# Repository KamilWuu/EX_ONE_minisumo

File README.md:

# EX_ONE_minisumo
# New dimension of minisumo robots.

faulhaber motors

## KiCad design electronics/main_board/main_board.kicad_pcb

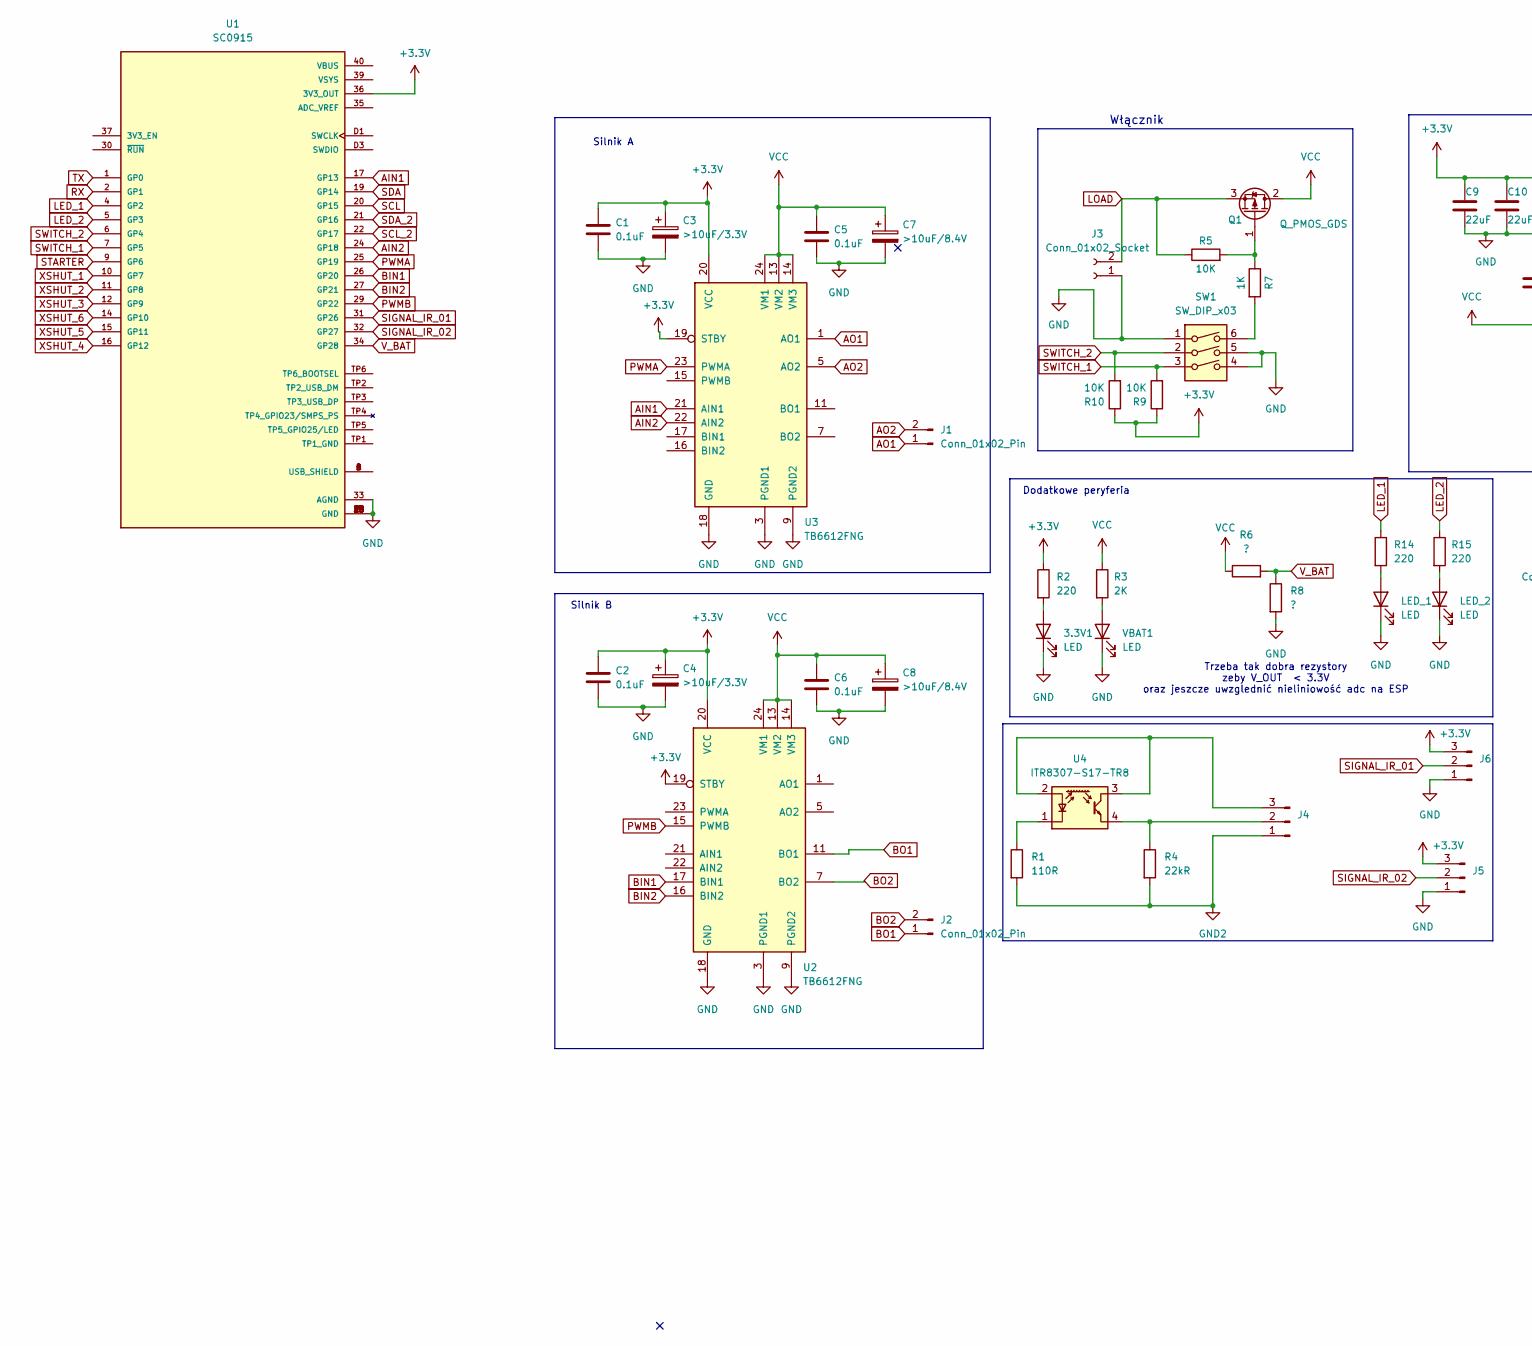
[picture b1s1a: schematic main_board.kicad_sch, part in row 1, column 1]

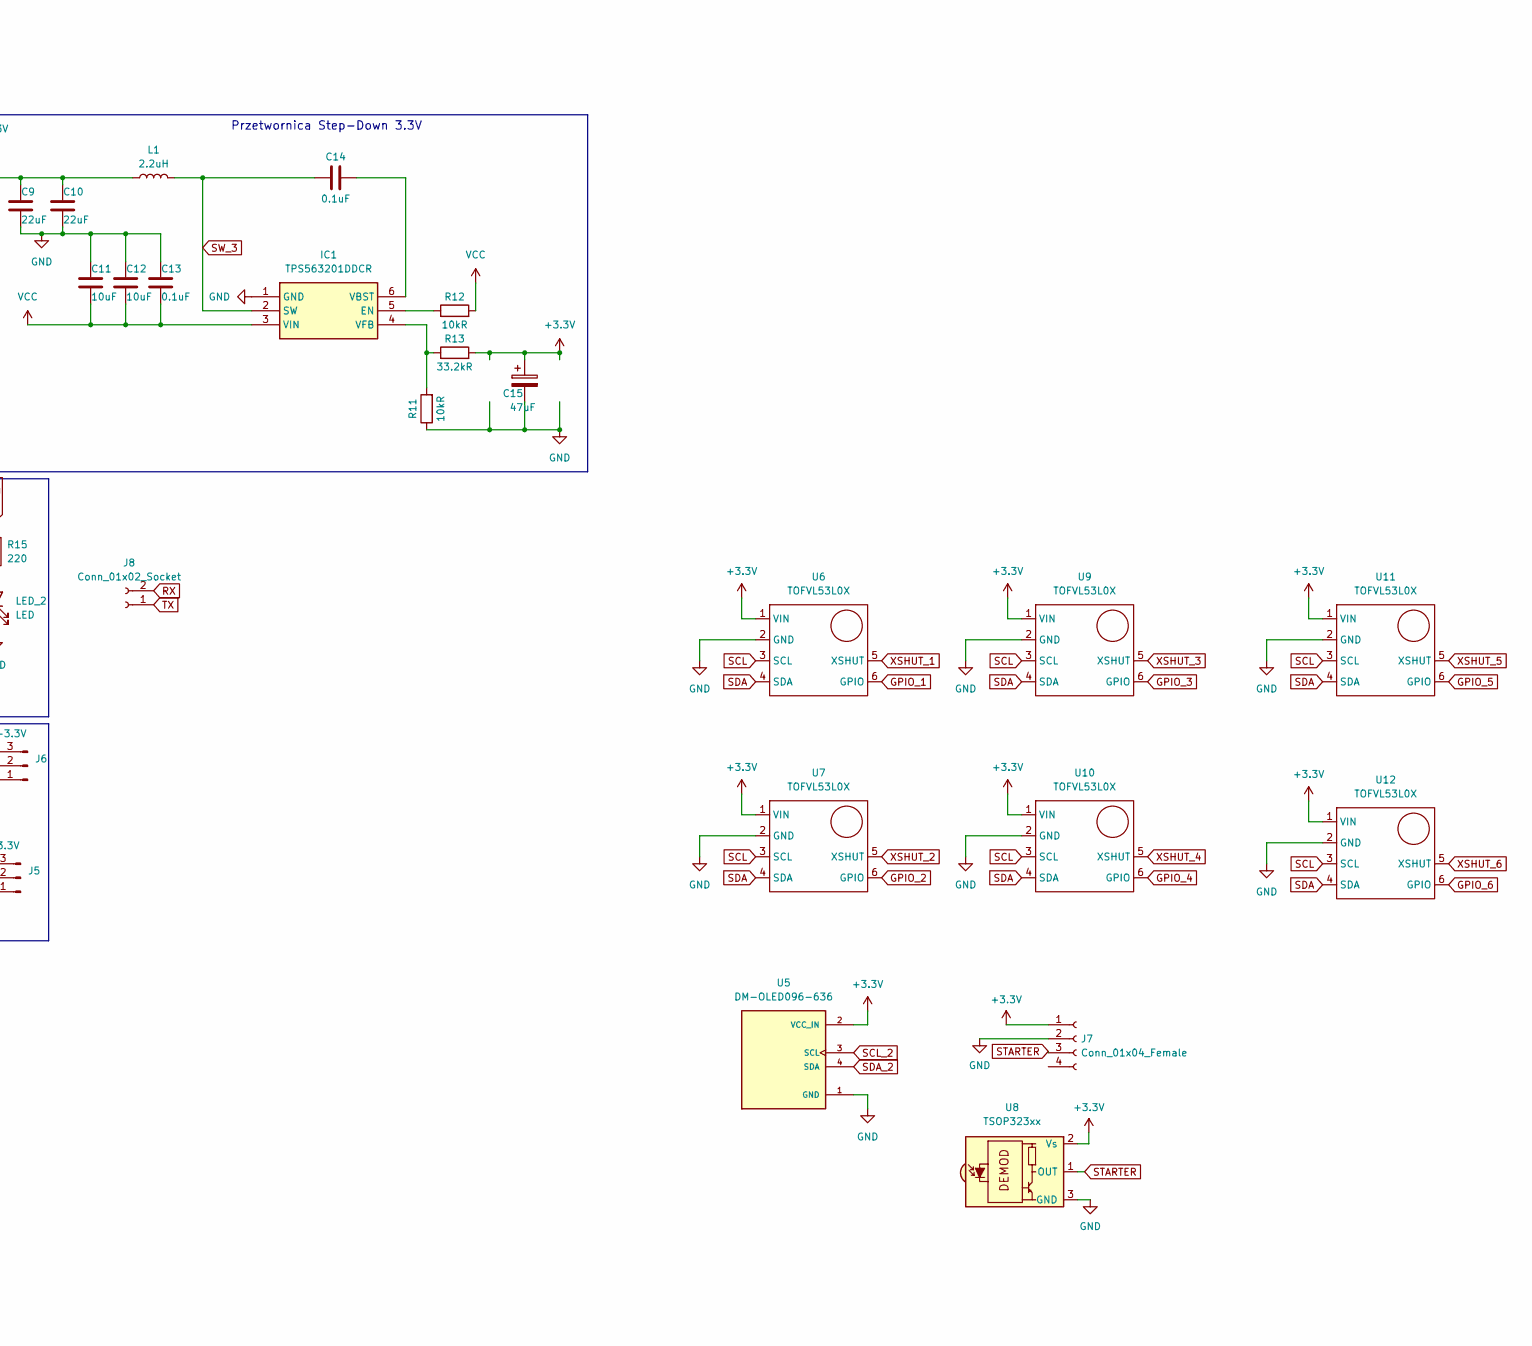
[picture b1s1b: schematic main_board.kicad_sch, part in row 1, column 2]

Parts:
3.3V1: LED; LED_0603_1608Metric
C1, C2, C5, C6, C13, C14: 0.1uF; C_0603_1608Metric
C3, C4: >10uF/3.3V; CP_EIA-3528-21_Kemet-B
C7, C8: >10uF/8.4V; CP_EIA-3528-21_Kemet-B
C9, C10: 22uF; C_0805_2012Metric
C11, C12: 10uF; C_0805_2012Metric
C15: 47uF; CP_EIA-3528-21_Kemet-B_Pad1.50x2.35mm_HandSolder
IC1: TPS563201DDCR; SOT-23-6; Manufacturer_Part_Number TPS563201DDCR
J1, J2: Conn_01x02_Pin; JST_XA_B02B-XASK-1_1x02_P2.50mm_Vertical
J3, J8: Conn_01x02_Socket; PinHeader_1x02_P2.54mm_Vertical
J4, J5, J6: Conn_01x03_Pin; PinSocket_1x03_P2.54mm_Vertical
J7: Conn_01x04_Female; PinSocket_1x04_P2.54mm_Vertical
L1: 2.2uH; L_Bourns_SRP7028A_7.3x6.6mm
LED_1, LED_2: LED; LED_0603_1608Metric
Q1: Q_PMOS_GDS; DFN-8-1EP_6x5mm_P1.27mm_EP4x4mm
R1: 110R; R_0402_1005Metric_Pad0.72x0.64mm_HandSolder
R2, R14, R15: 220; R_0603_1608Metric
R3: 2K; R_0603_1608Metric
R4: 22kR; R_0402_1005Metric_Pad0.72x0.64mm_HandSolder
R5, R9, R10: 10K; R_0603_1608Metric
R6, R8: ?; R_0603_1608Metric
R7: 1K; R_0603_1608Metric
R11, R12: 10kR; R_0603_1608Metric
R13: 33.2kR; R_0603_1608Metric
SW1: SW_DIP_x03; SW_DIP_SPSTx03_Slide_6.7x9.18mm_W8.61mm_P2.54mm_LowProfile
U1: SC0915; MODULE_SC0918; PARTREV 1.9
U2, U3: TB6612FNG; SSOP-24_5.3x8.2mm_P0.65mm
U4: ITR8307-S17-TR8; Everlight_ITR1201SR10AR
U5: DM-OLED096-636; MODULE_DM-OLED096-636; PARTREV 2018-09-10
U6, U7, U9, U10, U11, U12: TOFVL53L0X
U8: TSOP323xx; Vishay_MOLD-3Pin
VBAT1: LED; LED_0603_1608Metric

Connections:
+3.3V: C1.1, C2.1, C3.1, C4.1, C9.2, C10.2, C15.1, J5.3, J6.3, J7.1, L1.1, R2.1, R9.1, R10.1, R13.2, U1.36 (3V3_OUT), U2.19 (STBY), U2.20 (VCC), U3.19 (STBY), U3.20 (VCC), U5.2 (VCC_IN), U6.1 (VIN), U7.1 (VIN), U8.2 (Vs), U9.1 (VIN), U10.1 (VIN), U11.1 (VIN), U12.1 (VIN)
AIN1: U1.17 (GP13), U3.21 (AIN1)
AIN2: U1.24 (GP18), U3.22 (AIN2)
AO1: J1.1, U3.1 (AO1), U3.2 (AO1)
AO2: J1.2, U3.5 (AO2), U3.6 (AO2)
BIN1: U1.26 (GP20), U2.17 (BIN1)
BIN2: U1.27 (GP21), U2.16 (BIN2)
BO1: J2.1, U2.11 (BO1), U2.12 (BO1)
BO2: J2.2, U2.7 (BO2), U2.8 (BO2)
GND: 3.3V1.1 (K), C1.2, C2.2, C3.2, C4.2, C5.2, C6.2, C7.2, C8.2, C9.1, C10.1, C11.2, C12.2, C13.2, C15.2, IC1.1 (GND), J3.1, J5.1, J6.1, J7.2, LED_1.1 (K), LED_2.1 (K), R8.2, R11.1, SW1.1, SW1.4, SW1.5, U1.3 (GND), U1.8 (GND), U1.13 (GND), U1.18 (GND), U1.23 (GND), U1.28 (GND), U1.33 (AGND), U1.38 (GND), U1.D2 (GND), U2.3 (PGND1), U2.4 (PGND1), U2.9 (PGND2), U2.10 (PGND2), U2.18 (GND), U3.3 (PGND1), U3.4 (PGND1), U3.9 (PGND2), U3.10 (PGND2), U3.18 (GND), U5.1 (GND), U6.2 (GND), U7.2 (GND), U8.3 (GND), U9.2 (GND), U10.2 (GND), U11.2 (GND), U12.2 (GND), VBAT1.1 (K); also elsewhere on the board
GND2: J4.1, R1.2, R4.2
GPIO_1: U6.6 (GPIO)
GPIO_2: U7.6 (GPIO)
GPIO_3: U9.6 (GPIO)
GPIO_4: U10.6 (GPIO)
GPIO_5: U11.6 (GPIO)
GPIO_6: U12.6 (GPIO)
LED_1: R14.1, U1.4 (GP2)
LED_2: R15.1, U1.5 (GP3)
LOAD: J3.2, Q1.3 (S), R5.1
unnamed 20: 3.3V1.2 (A), R2.2; also elsewhere on the board
unnamed: IC1.5 (EN), R12.1
unnamed: C14.2, IC1.6 (VBST)
unnamed: IC1.4 (VFB), R11.2, R13.1
unnamed: J4.2, R4.1, U4.4
unnamed: J4.3, U4.2 (A), U4.3
unnamed: LED_1.2 (A), R14.2
unnamed: LED_2.2 (A), R15.2
unnamed: Q1.1 (G), R5.2, R7.1
unnamed: R7.2, SW1.6
unnamed: U1.A (USB_SHIELD), U1.B (USB_SHIELD), U1.C (USB_SHIELD), U1.D (USB_SHIELD)
unnamed: U2.1 (AO1), U2.2 (AO1)
unnamed: U2.5 (AO2), U2.6 (AO2)
unnamed: U3.11 (BO1), U3.12 (BO1)
unnamed: U3.7 (BO2), U3.8 (BO2)
unnamed: R1.1, U4.1 (K)
unnamed 36: R3.2, VBAT1.2 (A); also elsewhere on the board
PWMA: U1.25 (GP19), U3.23 (PWMA)
PWMB: U1.29 (GP22), U2.15 (PWMB)
RX: J8.2, U1.2 (GP1)
SCL: U1.20 (GP15), U6.3 (SCL), U7.3 (SCL), U9.3 (SCL), U10.3 (SCL), U11.3 (SCL), U12.3 (SCL)
SCL_2: U1.22 (GP17), U5.3 (SCL)
SDA: U1.19 (GP14), U6.4 (SDA), U7.4 (SDA), U9.4 (SDA), U10.4 (SDA), U11.4 (SDA), U12.4 (SDA)
SDA_2: U1.21 (GP16), U5.4 (SDA)
SIGNAL_IR_01: J6.2, U1.31 (GP26)
SIGNAL_IR_02: J5.2, U1.32 (GP27)
STARTER: J7.3, U1.9 (GP6), U8.1 (OUT)
SWITCH_1: R9.2, SW1.3, U1.7 (GP5)
SWITCH_2: R10.2, SW1.2, U1.6 (GP4)
SW_3: C14.1, IC1.2 (SW), L1.2
TX: J8.1, U1.1 (GP0)
VCC: C5.1, C6.1, C7.1, C8.1, C11.1, C12.1, C13.1, IC1.3 (VIN), Q1.2 (D), R3.1, R6.1, R12.2, U2.13 (VM2), U2.14 (VM3), U2.24 (VM1), U3.13 (VM2), U3.14 (VM3), U3.24 (VM1)
V_BAT: R6.2, R8.1, U1.34 (GP28)
XSHUT_1: U1.10 (GP7), U6.5 (XSHUT)
XSHUT_2: U1.11 (GP8), U7.5 (XSHUT)
XSHUT_3: U1.12 (GP9), U9.5 (XSHUT)
XSHUT_4: U1.16 (GP12), U10.5 (XSHUT)
XSHUT_5: U1.15 (GP11), U11.5 (XSHUT)
XSHUT_6: U1.14 (GP10), U12.5 (XSHUT)

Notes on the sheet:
Przetwornica Step-Down 3.3V
Dodatkowe peryferia
Silnik B
Silnik A
Trzeba tak dobra rezystory zeby V_OUT < 3.3V oraz jeszcze uwzglednić nieliniowość adc na ESP
Włącznik

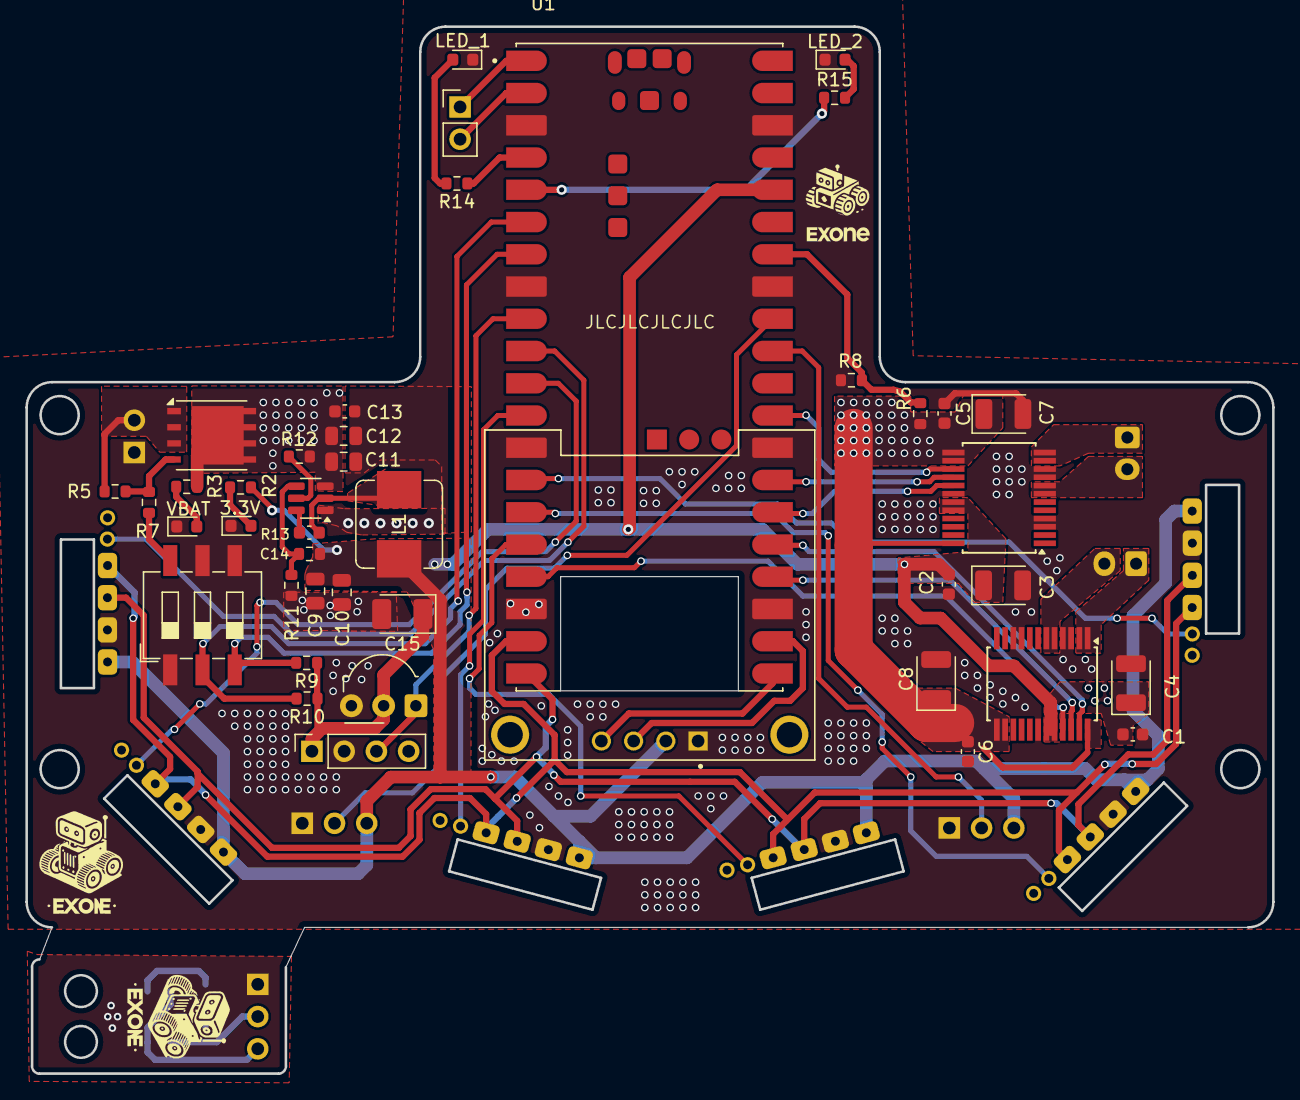
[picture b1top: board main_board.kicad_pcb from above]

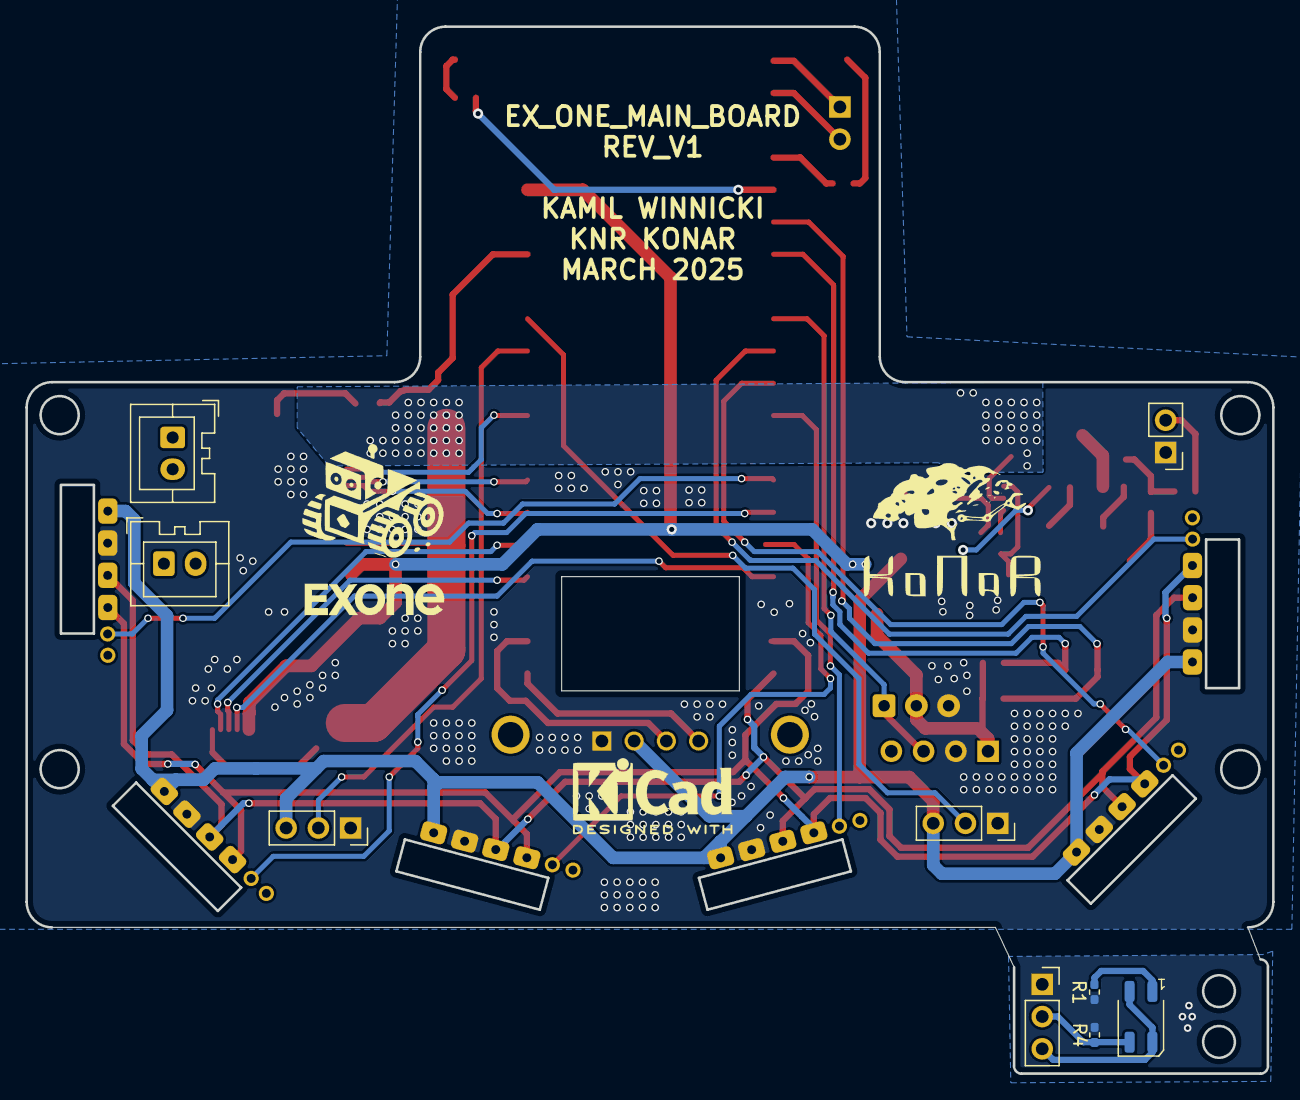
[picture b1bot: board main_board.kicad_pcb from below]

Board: 2 copper layers, 98.2 x 82.5 mm, 58 parts (9 on the bottom side), 53 nets.

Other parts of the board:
3.3V: LED; LED_0603_1608Metric
VBAT: LED; LED_0603_1608Metric

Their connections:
GND: 3.3V.1 (K), VBAT.1 (K); also elsewhere on the board
unnamed 20: 3.3V.2 (A); also elsewhere on the board
unnamed 36: VBAT.2 (A); also elsewhere on the board

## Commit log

2025-01-11 utworzono repozytorium
2025-01-15 mechanika
2025-01-15 elektronika
2025-01-19 elektronika wstepnie skonczona
2025-03-03 elekto
2025-03-06 elektro2
2025-03-06 skonczono plytke
2025-03-12 zmiany mechaniki 1
2025-03-12 dalsza mechanika
2025-03-16 readme
2025-03-16 readme2
2025-03-20 mechanika cos tam
